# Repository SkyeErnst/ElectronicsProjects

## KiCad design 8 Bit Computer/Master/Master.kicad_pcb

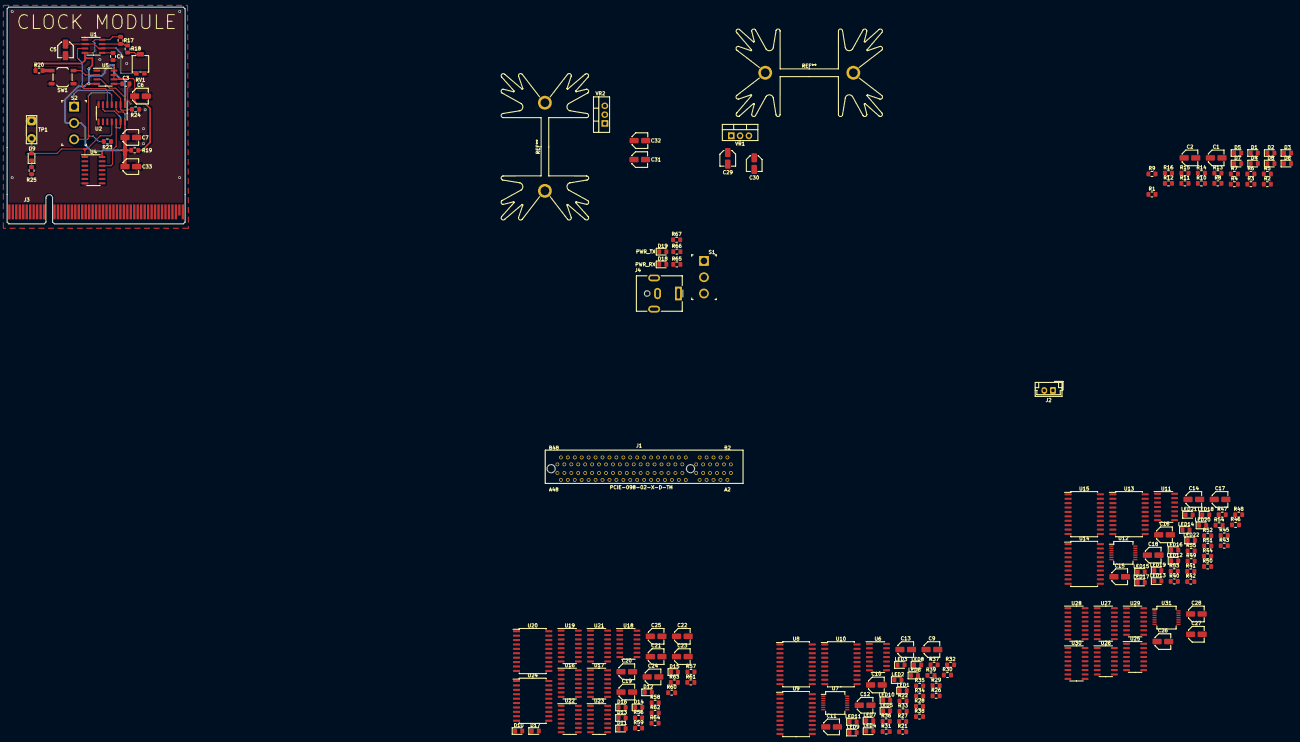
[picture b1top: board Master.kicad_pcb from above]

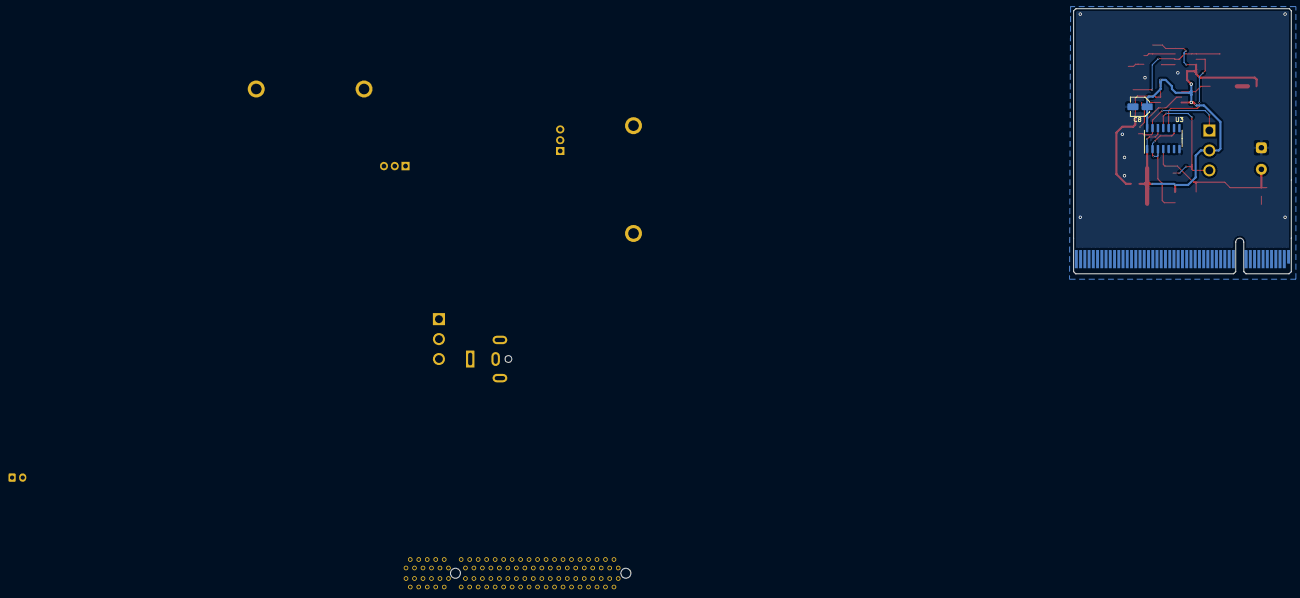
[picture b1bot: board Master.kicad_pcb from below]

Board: 2 copper layers, 51.3 x 62.5 mm, 183 parts (2 on the bottom side), 258 nets.

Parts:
C1, C2, C6: 0.1uF; C_Elec_4x5.4
C3, C4: 0.01uF; C_0805_2012Metric_Pad1.15x1.40mm_HandSolder
C5, C7, C8, C9, C10, C11, C12, C13, C14, C15, C16, C17, C18, C19, C20, C21, C22, C23, C24, C25, C26, C27, C28, C30, C32, C33: 1uF; C_Elec_4x5.4
C29, C31: 0.47uF; C_Elec_4x5.4
D1, D2, D3, D4, D5, D6, D7, D8, D18: GREEN; LED_0805_2012Metric_Pad1.15x1.40mm_HandSolder
D9, D10, D11, D12, D13, D14, D15, D16, D17: LED; LED_0805_2012Metric_Pad1.15x1.40mm_HandSolder
D19: RED; LED_0805_2012Metric_Pad1.15x1.40mm_HandSolder
J1: PCIE-098-02-X-D-TH
J2: PWR_IN 1x2 MALE; JST_EH_B2B-EH-A_1x02_P2.50mm_Vertical
J3: PCIE-098-02-X-D-TH; BUS_PCIexpress_x8
J4: PJ-063AH; BarrelJack_CUI_PJ-063AH_Horizontal
LED1, LED2, LED3, LED4, LED5, LED6, LED7, LED8, LED12, LED13, LED14, LED15, LED16, LED17, LED18, LED19: LED_Small; LED_0805_2012Metric_Pad1.15x1.40mm_HandSolder
LED9, LED20: BUS_READ; LED_0805_2012Metric_Pad1.15x1.40mm_HandSolder
LED10, LED21: REG_WRITE; LED_0805_2012Metric_Pad1.15x1.40mm_HandSolder
LED11, LED22: BUS_WRITE; LED_0805_2012Metric_Pad1.15x1.40mm_HandSolder
R1, R2, R3, R4, R5, R6, R7, R8, R21, R22, R25, R26, R27, R28, R29, R30, R31, R37, R38, R39, R40, R41, R42, R43, R44, R45, R46, R47, R53, R54, R55, R57, R58, R59, R60, R61, R62, R63, R64: 220; R_0805_2012Metric_Pad1.15x1.40mm_HandSolder
R9, R10, R11, R12, R13, R14, R15, R16: 10K; R_0805_2012Metric_Pad1.15x1.40mm_HandSolder
R17, R18, R20, R32, R33, R34, R35, R36, R48, R49, R50, R51, R52: 1k; R_0805_2012Metric_Pad1.15x1.40mm_HandSolder
R19: 1M; R_0805_2012Metric_Pad1.15x1.40mm_HandSolder
R23, R24: 2k; R_0805_2012Metric_Pad1.15x1.40mm_HandSolder
R56: 10k; R_0805_2012Metric_Pad1.15x1.40mm_HandSolder
R65, R66: 680; R_0805_2012Metric_Pad1.15x1.40mm_HandSolder
R67: 100K; R_0805_2012Metric_Pad1.15x1.40mm_HandSolder
RV1: 1M; Potentiometer_Bourns_3314G_Vertical
S1, S2: 100SP1T1B4M2QE; Toggle_Switch_100SP1T1B4M2QE
SW1: SW_Push; SW_SPST_TL3342
TP1: CLK_TP; TestPoint_2Pads_Pitch5.08mm_Drill1.3mm
U1, U5: NE555; SOIC-8_3.9x4.9mm_P1.27mm
U2: SN74LS08N; SOIC-14_3.9x8.7mm_P1.27mm
U3: SN74LS32N; SOIC-14_3.9x8.7mm_P1.27mm
U4: SN74LS04N; SOIC-14_3.9x8.7mm_P1.27mm
U6, U11, U25, U26, U29: 74LS08; SOIC-14_3.9x8.7mm_P1.27mm
U7, U12: 74LS04; SSOP-14_5.3x6.2mm_P0.65mm
U8, U10, U13, U15, U20, U24: 74LS245; SOIC-20W_7.5x12.8mm_P1.27mm
U9, U14: 74LS273; SOIC-20W_7.5x12.8mm_P1.27mm
U16: 74LS32; SOIC-14_3.9x8.7mm_P1.27mm
U17, U18, U22, U23: 74LS86; SOIC-14_3.9x8.7mm_P1.27mm
U19, U21, U27, U28, U30: 74LS283; SOIC-16_3.9x9.9mm_P1.27mm
U31: 74LS08; SSOP-14_5.3x6.2mm_P0.65mm
VR1, VR2: L78S05CV; TO-220-3_Vertical

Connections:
+5V: C1.1, C2.1, C7.1, C8.1, C9.1, C10.1, C11.1, C12.1, C13.1, C14.1, C15.1, C16.1, C17.1, C18.1, C30.1, C32.1, C33.1, J2.1, R17.1, R19.1, R20.1, R33.1, R49.1, R56.2, S2.2, U1.4, U1.8, U2.14, U3.14, U4.14, U5.4, U5.8, U6.14, U7.14, U8.1, U8.20, U9.20, U10.1, U10.20, U11.14, U12.14, U13.1, U13.20, U14.20, U15.1, U15.20, U20.1, U24.1, VR1.3, VR2.3
/BUS_0: R1.2, R9.1
/BUS_1: R2.2, R10.1
/BUS_2: R3.2, R11.1
/BUS_3: R4.2, R12.1
/BUS_4: R5.2, R13.1
/BUS_5: R6.2, R14.1
/BUS_6: R7.2, R15.1
/BUS_7: R8.2, R16.1
/Clock/CLK: D9.2, J3.A1, TP1.2, U2.11, U4.1
/Clock/HAULT: J3.A3, J3.B3, U4.13
/Clock/LNE_4: J3.A4, J3.B4
/Clock/LNE_5: J3.A5, J3.B5
/Clock/LNE_6: J3.A6, J3.B6
/Clock/LNE_7: J3.A7, J3.B7
/Clock/LNE_8: J3.A8, J3.B8
/Clock/LNE_9: J3.A9, J3.B9
/Clock/LNE_10: J3.A10, J3.B10
/Clock/LNE_11: J3.A11, J3.B11
/Clock/LNE_12: J3.A12, J3.B12
/Clock/LNE_13: J3.A13, J3.B13
/Clock/LNE_14: J3.A14, J3.B14
/Clock/LNE_15: J3.A15, J3.B15
/Clock/LNE_16: J3.A16, J3.B16
/Clock/LNE_17: J3.A17, J3.B17
/Clock/LNE_18: J3.A18, J3.B18
/Clock/LNE_19: J3.A19, J3.B19
/Clock/LNE_20: J3.A20, J3.B20
/Clock/LNE_21: J3.A21, J3.B21
/Clock/LNE_22: J3.A22, J3.B22
/Clock/LNE_23: J3.A23, J3.B23
/Clock/LNE_24: J3.A24, J3.B24
/Clock/LNE_25: J3.A25, J3.B25
/Clock/LNE_26: J3.A26, J3.B26
/Clock/LNE_27: J3.A27, J3.B27
/Clock/LNE_28: J3.A28, J3.B28
/Clock/LNE_29: J3.A29, J3.B29
/Clock/LNE_30: J3.A30, J3.B30
/Clock/LNE_31: J3.A31, J3.B31
/Clock/LNE_32: J3.A32, J3.B32
/Clock/LNE_33: J3.A33, J3.B33
/Clock/LNE_34: J3.A34, J3.B34
/Clock/LNE_35: J3.A35, J3.B35
/Clock/LNE_36: J3.A36, J3.B36
/Clock/LNE_37: J3.A37, J3.B37
/Clock/LNE_38: J3.A38, J3.B38
/Clock/LNE_39: J3.A39, J3.B39
/Clock/LNE_40: J3.A40, J3.B40
/Clock/LNE_41: J3.A41, J3.B41
/Clock/LNE_42: J3.A42, J3.B42
/Clock/LNE_43: J3.A43, J3.B43
/Clock/LNE_44: J3.A44, J3.B44
/Clock/LNE_45: J3.A45, J3.B45
/Clock/LNE_46: J3.A46, J3.B46
/Clock/LNE_47: J3.A47, J3.B47
/Clock/LNE_48: J3.A48, J3.B48
/Clock/LNE_49: J3.A49, J3.B49
/Clock/~CLK: J3.A2, J3.B2, U4.2
/Math Unit A/REG_AA/ALU_AA_0: R21.2, U9.2, U10.2, U17.2, U25.2, U26.2, U29.2, U31.2
/Math Unit A/REG_AA/ALU_AA_1: R22.2, U6.5, U9.5, U10.3, U11.5, U17.5, U25.5, U26.5
/Math Unit A/REG_AA/ALU_AA_2: R26.2, U6.10, U9.6, U10.4, U11.10, U17.10, U25.10, U26.10
/Math Unit A/REG_AA/ALU_AA_3: R27.2, U6.13, U9.9, U10.5, U11.13, U17.13, U25.13, U26.13
/Math Unit A/REG_AA/ALU_AA_4: R28.2, U9.12, U10.6, U22.2
/Math Unit A/REG_AA/ALU_AA_5: R29.2, U9.15, U10.7, U22.5
/Math Unit A/REG_AA/ALU_AA_6: R30.2, U9.16, U10.8, U22.10
/Math Unit A/REG_AA/ALU_AA_7: R31.2, U9.19, U10.9, U22.13
/Math Unit A/REG_AA/BUS_0: U8.2, U10.18
/Math Unit A/REG_AA/BUS_1: U8.3, U10.17
/Math Unit A/REG_AA/BUS_2: U8.4, U10.16
/Math Unit A/REG_AA/BUS_3: U8.5, U10.15
/Math Unit A/REG_AA/BUS_4: U8.6, U10.14
/Math Unit A/REG_AA/BUS_5: U8.7, U10.13
/Math Unit A/REG_AA/BUS_6: U8.8, U10.12
/Math Unit A/REG_AA/BUS_7: U8.9, U10.11
/Math Unit A/REG_AA/CLK: R36.2, U6.2
/Math Unit A/REG_AA/REG_A_BUS_READ: R32.2, R35.2, U6.1, U7.1, U8.19
/Math Unit A/REG_AA/REG_A_BUS_WRITE: U7.3, U10.19
/Math Unit A/REG_AA/RESET: R33.2, U9.1
/Math Unit A/REG_AB/ALU_AB_0: R40.2, U14.2, U15.2, U18.2, U25.4, U25.9, U25.12, U29.1
/Math Unit A/REG_AB/ALU_AB_1: R41.2, U14.5, U15.3, U18.5, U26.4, U26.9, U26.12, U31.1
/Math Unit A/REG_AB/ALU_AB_2: R42.2, U11.4, U11.9, U11.12, U14.6, U15.4, U18.10, U26.1
/Math Unit A/REG_AB/ALU_AB_3: R43.2, U6.4, U6.9, U6.12, U14.9, U15.5, U18.13, U25.1
/Math Unit A/REG_AB/ALU_AB_4: R44.2, U14.12, U15.6, U23.2
/Math Unit A/REG_AB/ALU_AB_5: R45.2, U14.15, U15.7, U23.5
/Math Unit A/REG_AB/ALU_AB_6: R46.2, U14.16, U15.8, U23.10
/Math Unit A/REG_AB/ALU_AB_7: R47.2, U14.19, U15.9, U23.13
/Math Unit A/REG_AB/BUS_0: U13.2, U15.18
/Math Unit A/REG_AB/BUS_1: U13.3, U15.17
/Math Unit A/REG_AB/BUS_2: U13.4, U15.16
/Math Unit A/REG_AB/BUS_3: U13.5, U15.15
/Math Unit A/REG_AB/BUS_4: U13.6, U15.14
/Math Unit A/REG_AB/BUS_5: U13.7, U15.13
/Math Unit A/REG_AB/BUS_6: U13.8, U15.12
/Math Unit A/REG_AB/BUS_7: U13.9, U15.11
/Math Unit A/REG_AB/CLK: R52.2, U11.2
/Math Unit A/REG_AB/REG_B_BUS_READ: R48.2, R51.2, U11.1, U12.1, U13.19
/Math Unit A/REG_AB/REG_B_BUS_WRITE: R50.2, U12.3, U15.19
/Math Unit A/REG_AB/RESET: R49.2, U14.1
/Math Unit A/sheet5E11EF59/BUS_0: U20.18, U24.18
/Math Unit A/sheet5E11EF59/BUS_1: U20.17, U24.17
/Math Unit A/sheet5E11EF59/BUS_2: U20.16, U24.16
/Math Unit A/sheet5E11EF59/BUS_3: U20.15, U24.15
/Math Unit A/sheet5E11EF59/BUS_4: U20.14, U24.14
/Math Unit A/sheet5E11EF59/BUS_5: U20.13, U24.13
/Math Unit A/sheet5E11EF59/BUS_6: U20.12, U24.12
/Math Unit A/sheet5E11EF59/BUS_7: U20.11, U24.11
/Math Unit A/sheet5E11EF59/Multiplier/MUL_0: U24.2, U29.3
/Math Unit A/sheet5E11EF59/Multiplier/MUL_1: U24.3, U30.4
/Math Unit A/sheet5E11EF59/Multiplier/MUL_2: U24.4, U28.4
/Math Unit A/sheet5E11EF59/Multiplier/MUL_3: U24.5, U27.4
/Math Unit A/sheet5E11EF59/Multiplier/MUL_4: U24.6, U27.1
/Math Unit A/sheet5E11EF59/Multiplier/MUL_5: U24.7, U27.13
/Math Unit A/sheet5E11EF59/Multiplier/MUL_6: U24.8, U27.10
/Math Unit A/sheet5E11EF59/Multiplier/MUL_7: U24.9, U27.9
/Math Unit A/sheet5E11EF59/SUBa: U16.1, U17.1, U17.4, U17.9, U17.12, U22.1, U22.4, U22.9, U22.12
/Math Unit A/sheet5E11EF59/SUBb: U16.2, U18.1, U18.4, U18.9, U18.12, U23.1, U23.4, U23.9, U23.12
/Math Unit A/sheet5E11EF59/~EOas: R56.1, U20.19
/POWR/PWR_AFT_SW: C29.1, C31.1, R66.2, S1.2, VR1.1, VR2.1
/POWR/PWR_IN: J4.1, R65.2, S1.3
GND: C1.2, C2.2, C3.2, C4.2, C5.2, C6.2, C7.2, C8.2, C9.2, C10.2, C11.2, C12.2, C13.2, C14.2, C15.2, C16.2, C17.2, C18.2, C19.2, C20.2, C21.2, C22.2, C23.2, C24.2, C25.2, C26.2, C27.2, C28.2, C29.2, C30.2, C31.2, C32.2, C33.2, D1.1, D2.1, D3.1, D4.1, D5.1, D6.1, D7.1, D8.1, D10.1, D11.1, D12.1, D13.1, D14.1, D15.1, D16.1, D17.1, D18.1, D19.1, J2.2, J4.2, LED1.1, LED2.1, LED3.1, LED4.1, LED5.1, LED6.1, LED7.1, LED8.1, LED9.1, LED10.1, LED11.1, LED12.1, LED13.1, LED14.1, LED15.1, LED16.1, LED17.1, LED18.1, LED19.1, LED20.1, LED21.1, LED22.1, R9.2, R10.2, R11.2, R12.2, R13.2, R14.2, R15.2, R16.2, R23.1, R24.1, R25.1, R32.1, R34.1, R35.1, R36.1, R48.1, R50.1, R51.1, R52.1, R67.1, SW1.1, TP1.1, U1.1, U2.7, U3.7, U4.7, U5.1, U6.7, U7.7, U8.10, U9.10, U10.10, U11.7, U12.7, U13.10, U14.10, U15.10, U16.7, U17.7, U18.7, U19.8, U20.10, U21.8, U24.10, U27.7, U27.8, U28.7, U28.8, U30.7, U30.8, U30.12, VR1.2, VR2.2
unnamed: C3.1, U5.5
unnamed: C4.1, U1.5
unnamed: C5.1, RV1.1, U1.2, U1.6
unnamed: C6.1, R19.2, U5.6, U5.7
unnamed: C19.1, U16.14
unnamed: C20.1, U17.14
unnamed: C21.1, U18.14
unnamed: C22.1, U19.16
unnamed: C23.1, U20.20
unnamed: C24.1, U21.16
unnamed: C25.1, U24.20
unnamed: C26.1, U27.16
unnamed: C27.1, U28.16
unnamed: C28.1, U30.16
unnamed: D1.2, R1.1
unnamed: D2.2, R2.1
unnamed: D3.2, R3.1
unnamed: D4.2, R4.1
unnamed: D5.2, R5.1
unnamed: D6.2, R6.1
unnamed: D7.2, R7.1
unnamed: D8.2, R8.1
unnamed: D9.1, R25.2
unnamed: D10.2, R57.2
unnamed: D11.2, R58.2
unnamed: D12.2, R59.2
unnamed: D13.2, R60.2
unnamed: D14.2, R61.2
unnamed: D15.2, R62.2
unnamed: D16.2, R63.2
unnamed: D17.2, R64.2
unnamed: D18.2, R65.1
unnamed: D19.2, R66.1
unnamed: LED1.2, R21.1
unnamed: LED2.2, R22.1
unnamed: LED3.2, R26.1
unnamed: LED4.2, R27.1
unnamed: LED5.2, R28.1
unnamed: LED6.2, R29.1
unnamed: LED7.2, R30.1
unnamed: LED8.2, R31.1
unnamed: LED9.2, R37.1
unnamed: LED10.2, R38.1
unnamed: LED11.2, R39.1
unnamed: LED12.2, R40.1
unnamed: LED13.2, R41.1
unnamed: LED14.2, R42.1
unnamed: LED15.2, R43.1
unnamed: LED16.2, R44.1
unnamed: LED17.2, R45.1
unnamed: LED18.2, R46.1
unnamed: LED19.2, R47.1
unnamed: LED20.2, R53.1
unnamed: LED21.2, R54.1
unnamed: LED22.2, R55.1
unnamed: R17.2, R18.2, U1.7
unnamed: R18.1, RV1.2
unnamed: R20.2, SW1.2, U5.2
unnamed: R23.2, S2.3, U2.4
unnamed: R24.2, S2.1, U2.2
unnamed: R37.2, U7.2
unnamed: R38.2, U6.3, U9.11
unnamed: R39.2, U7.4
unnamed: R53.2, U12.2
unnamed: R54.2, U11.3, U14.11
unnamed: R55.2, U12.4
unnamed: R57.1, U19.4, U20.2
unnamed: R58.1, U19.1, U20.3
unnamed: R59.1, U19.13, U20.4
unnamed: R60.1, U19.10, U20.5
unnamed: R61.1, U20.6, U21.4
unnamed: R62.1, U20.7, U21.1
unnamed: R63.1, U20.8, U21.13
unnamed: R64.1, U20.9, U21.10
unnamed: R67.2, S1.1
unnamed: U1.3, U2.5
unnamed: U2.1, U5.3
unnamed: U2.3, U3.1
unnamed: U2.6, U3.2
unnamed: U2.12, U4.12
unnamed: U2.13, U3.3
unnamed: U8.11, U9.18
unnamed: U8.12, U9.17
unnamed: U8.13, U9.14
unnamed: U8.14, U9.13
unnamed: U8.15, U9.8
unnamed: U8.16, U9.7
unnamed: U8.17, U9.4
unnamed: U8.18, U9.3
unnamed: U11.6, U28.3
unnamed: U11.8, U28.14
unnamed: U11.11, U28.12
unnamed: U13.11, U14.18
unnamed: U13.12, U14.17
unnamed: U13.13, U14.14
unnamed: U13.14, U14.13
unnamed: U13.15, U14.8
unnamed: U13.16, U14.7
unnamed: U13.17, U14.4
unnamed: U13.18, U14.3
unnamed: U16.3, U19.7
unnamed: U17.3, U19.5
unnamed: U17.6, U19.3
unnamed: U17.8, U19.14
unnamed: U17.11, U19.12
unnamed: U18.3, U19.6
unnamed: U18.6, U19.2
unnamed: U18.8, U19.15
unnamed: U18.11, U19.11
unnamed: U19.9, U21.7
unnamed: U21.2, U23.6
unnamed: U21.3, U22.6
unnamed: U21.5, U22.3
unnamed: U21.6, U23.3
unnamed: U21.11, U23.11
unnamed: U21.12, U22.11
unnamed: U21.14, U22.8
unnamed: U21.15, U23.8
unnamed: U25.3, U27.5
unnamed: U25.6, U30.5
unnamed: U25.8, U30.3
unnamed: U25.11, U30.14
unnamed: U26.3, U28.5
unnamed: U26.6, U30.2
unnamed: U26.8, U30.15
unnamed: U26.11, U30.11
unnamed: U27.2, U28.13
unnamed: U6.6, U27.3
unnamed: U27.6, U28.1
unnamed: U27.11, U28.9
unnamed: U6.11, U27.12
unnamed: U6.8, U27.14
unnamed: U27.15, U28.10
unnamed: U28.2, U30.13
unnamed: U28.6, U30.1
unnamed: U28.11, U30.9
unnamed: U28.15, U30.10
unnamed: U30.6, U31.3

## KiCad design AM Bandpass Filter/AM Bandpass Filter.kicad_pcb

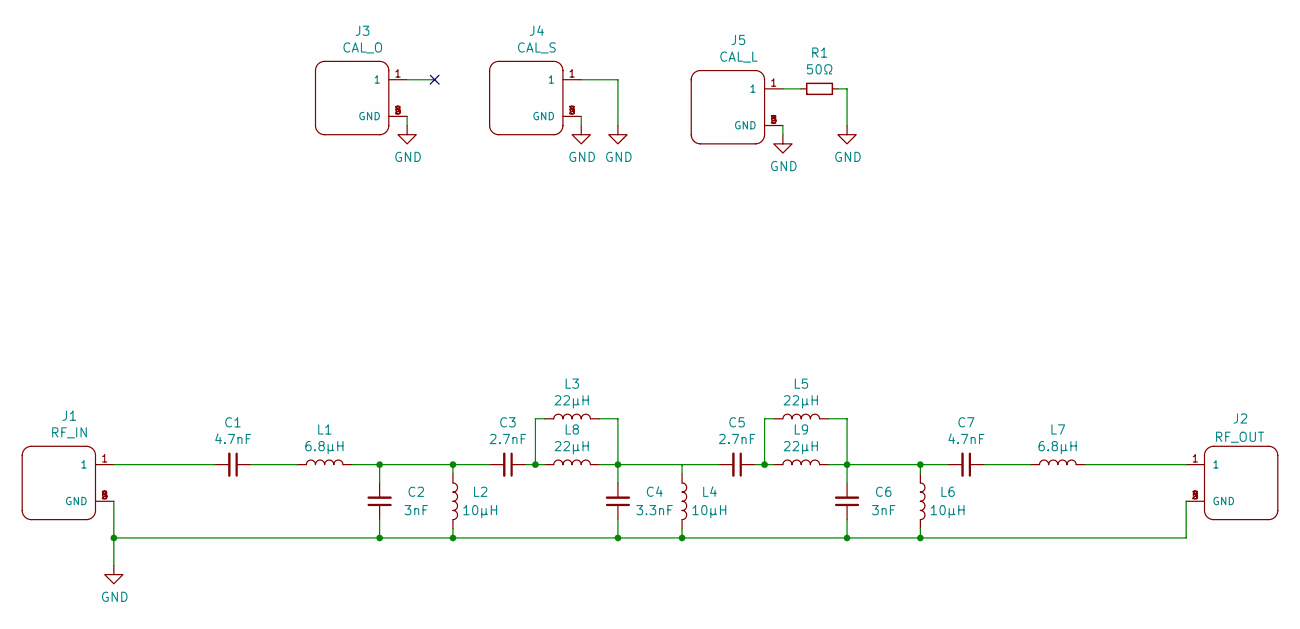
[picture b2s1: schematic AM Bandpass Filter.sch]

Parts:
C1, C7: 4.7nF; C_0805_2012Metric_Pad1.15x1.40mm_HandSolder
C2, C6: 3nF; C_0805_2012Metric_Pad1.15x1.40mm_HandSolder
C3, C5: 2.7nF; C_0805_2012Metric_Pad1.15x1.40mm_HandSolder
C4: 3.3nF; C_0805_2012Metric_Pad1.15x1.40mm_HandSolder
J1: RF_IN; TE_5-1634503-1
J2: RF_OUT; TE_5-1634503-1
J3: CAL_O; TE_5-1634503-1
J4: CAL_S; TE_5-1634503-1
J5: CAL_L; TE_5-1634503-1
L1, L7: 6.8µH; L_0805_2012Metric_Pad1.15x1.40mm_HandSolder
L2, L4, L6: 10µH; L_0805_2012Metric_Pad1.15x1.40mm_HandSolder
L3, L5, L8, L9: 22µH; L_0805_2012Metric_Pad1.15x1.40mm_HandSolder
R1: 50Ω; R_1206_3216Metric_Pad1.42x1.75mm_HandSolder

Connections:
GND: C2.1, C4.1, C6.1, J1.2 (GND), J1.3 (GND), J1.4 (GND), J1.5 (GND), J2.2 (GND), J2.3 (GND), J2.4 (GND), J2.5 (GND), J3.2 (GND), J3.3 (GND), J3.4 (GND), J3.5 (GND), J4.1, J4.2 (GND), J4.3 (GND), J4.4 (GND), J4.5 (GND), J5.2 (GND), J5.3 (GND), J5.4 (GND), J5.5 (GND), L2.2, L4.2, L6.2, R1.2
unnamed: C1.1, L1.1
unnamed: C1.2, J1.1
unnamed: C2.2, C3.2, L1.2, L2.1
unnamed: C3.1, L3.1, L8.1
unnamed: C4.2, C5.2, L3.2, L4.1, L8.2
unnamed: C5.1, L5.1, L9.1
unnamed: C6.2, C7.2, L5.2, L6.1, L9.2
unnamed: C7.1, L7.1
unnamed: J2.1, L7.2
unnamed: J5.1, R1.1

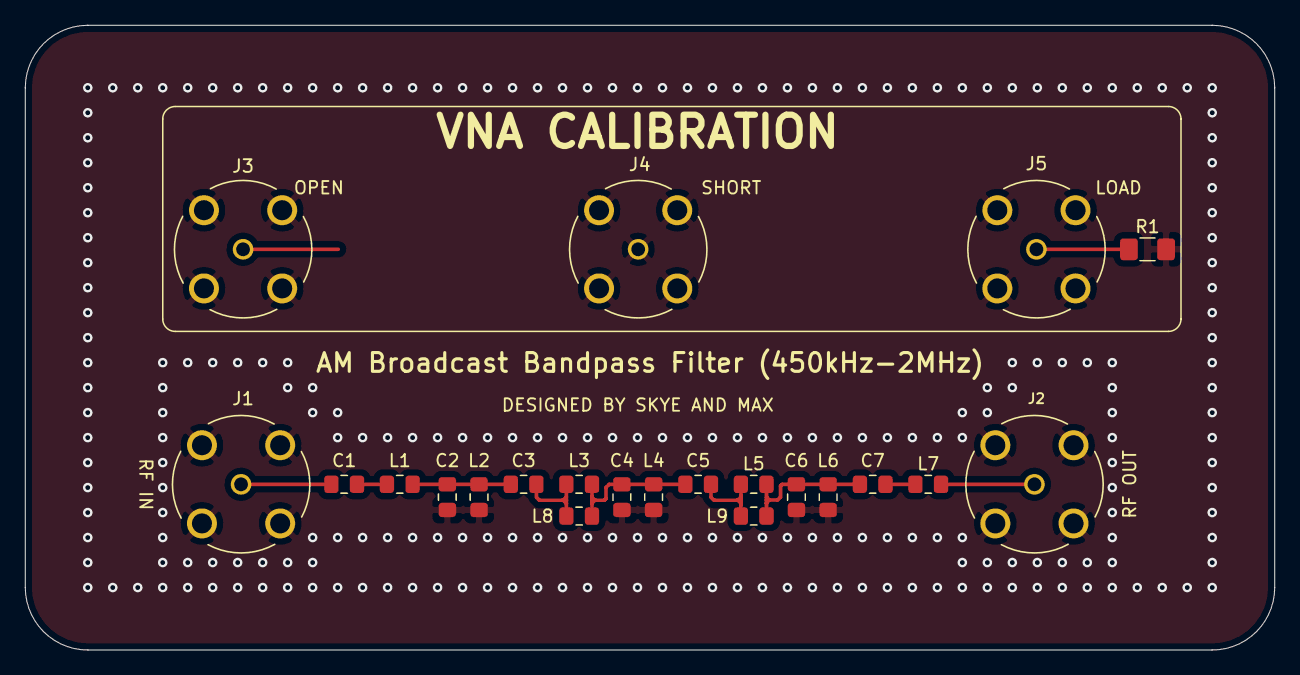
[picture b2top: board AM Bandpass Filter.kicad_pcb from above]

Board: 4 copper layers, 100.0 x 50.0 mm, 22 parts (0 on the bottom side), 11 nets.

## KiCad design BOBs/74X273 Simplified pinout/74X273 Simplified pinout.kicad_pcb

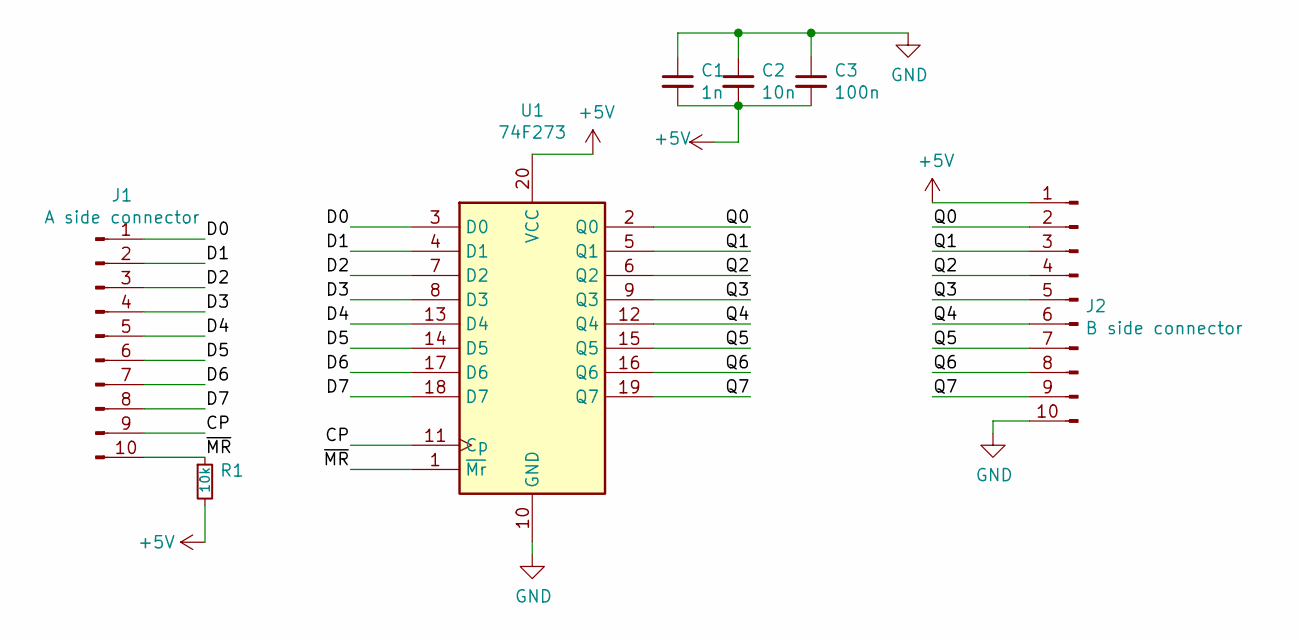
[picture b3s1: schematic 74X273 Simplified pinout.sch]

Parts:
C1: 1n; C_0805_2012Metric_Pad1.15x1.40mm_HandSolder
C2: 10n; C_0805_2012Metric_Pad1.15x1.40mm_HandSolder
C3: 100n; C_0805_2012Metric_Pad1.15x1.40mm_HandSolder
J1: A side connector; PinHeader_1x10_P2.54mm_Vertical
J2: B side connector; PinHeader_1x10_P2.54mm_Vertical
R1: 10k; R_0805_2012Metric
U1: 74F273; SOIC-20W_7.5x12.8mm_P1.27mm

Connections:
+5V: C1.2, C2.2, C3.2, J2.1, R1.2, U1.20 (VCC)
/CP: J1.9, U1.11 (Cp)
/D0: J1.1, U1.3 (D0)
/D1: J1.2, U1.4 (D1)
/D2: J1.3, U1.7 (D2)
/D3: J1.4, U1.8 (D3)
/D4: J1.5, U1.13 (D4)
/D5: J1.6, U1.14 (D5)
/D6: J1.7, U1.17 (D6)
/D7: J1.8, U1.18 (D7)
/Q0: J2.2, U1.2 (Q0)
/Q1: J2.3, U1.5 (Q1)
/Q2: J2.4, U1.6 (Q2)
/Q3: J2.5, U1.9 (Q3)
/Q4: J2.6, U1.12 (Q4)
/Q5: J2.7, U1.15 (Q5)
/Q6: J2.8, U1.16 (Q6)
/Q7: J2.9, U1.19 (Q7)
/~MR: J1.10, R1.1, U1.1 (~Mr)
GND: C1.1, C2.1, C3.1, J2.10, U1.10 (GND)

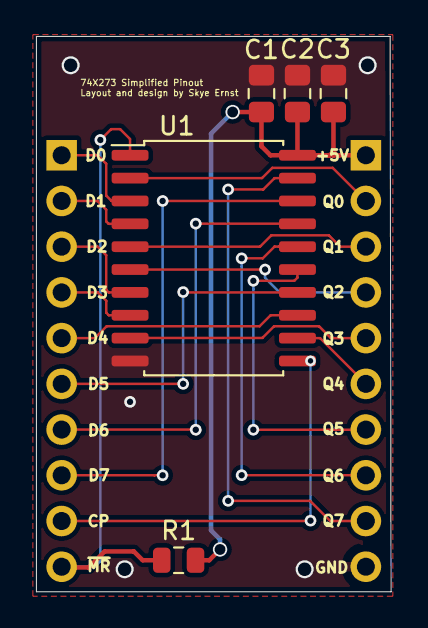
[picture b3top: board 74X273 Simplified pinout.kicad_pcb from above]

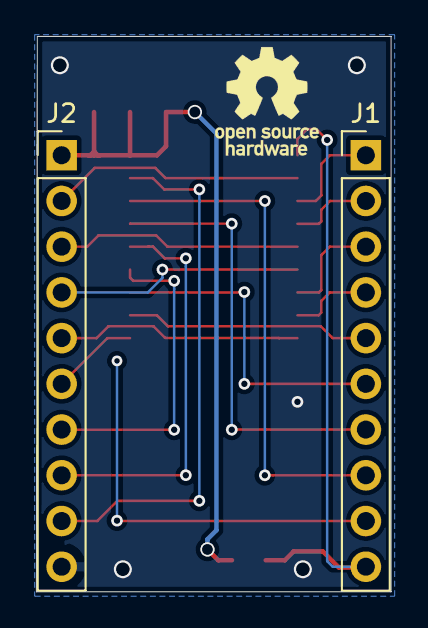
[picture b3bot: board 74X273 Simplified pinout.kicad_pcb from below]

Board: 2 copper layers, 19.7 x 30.8 mm, 7 parts (2 on the bottom side), 20 nets.

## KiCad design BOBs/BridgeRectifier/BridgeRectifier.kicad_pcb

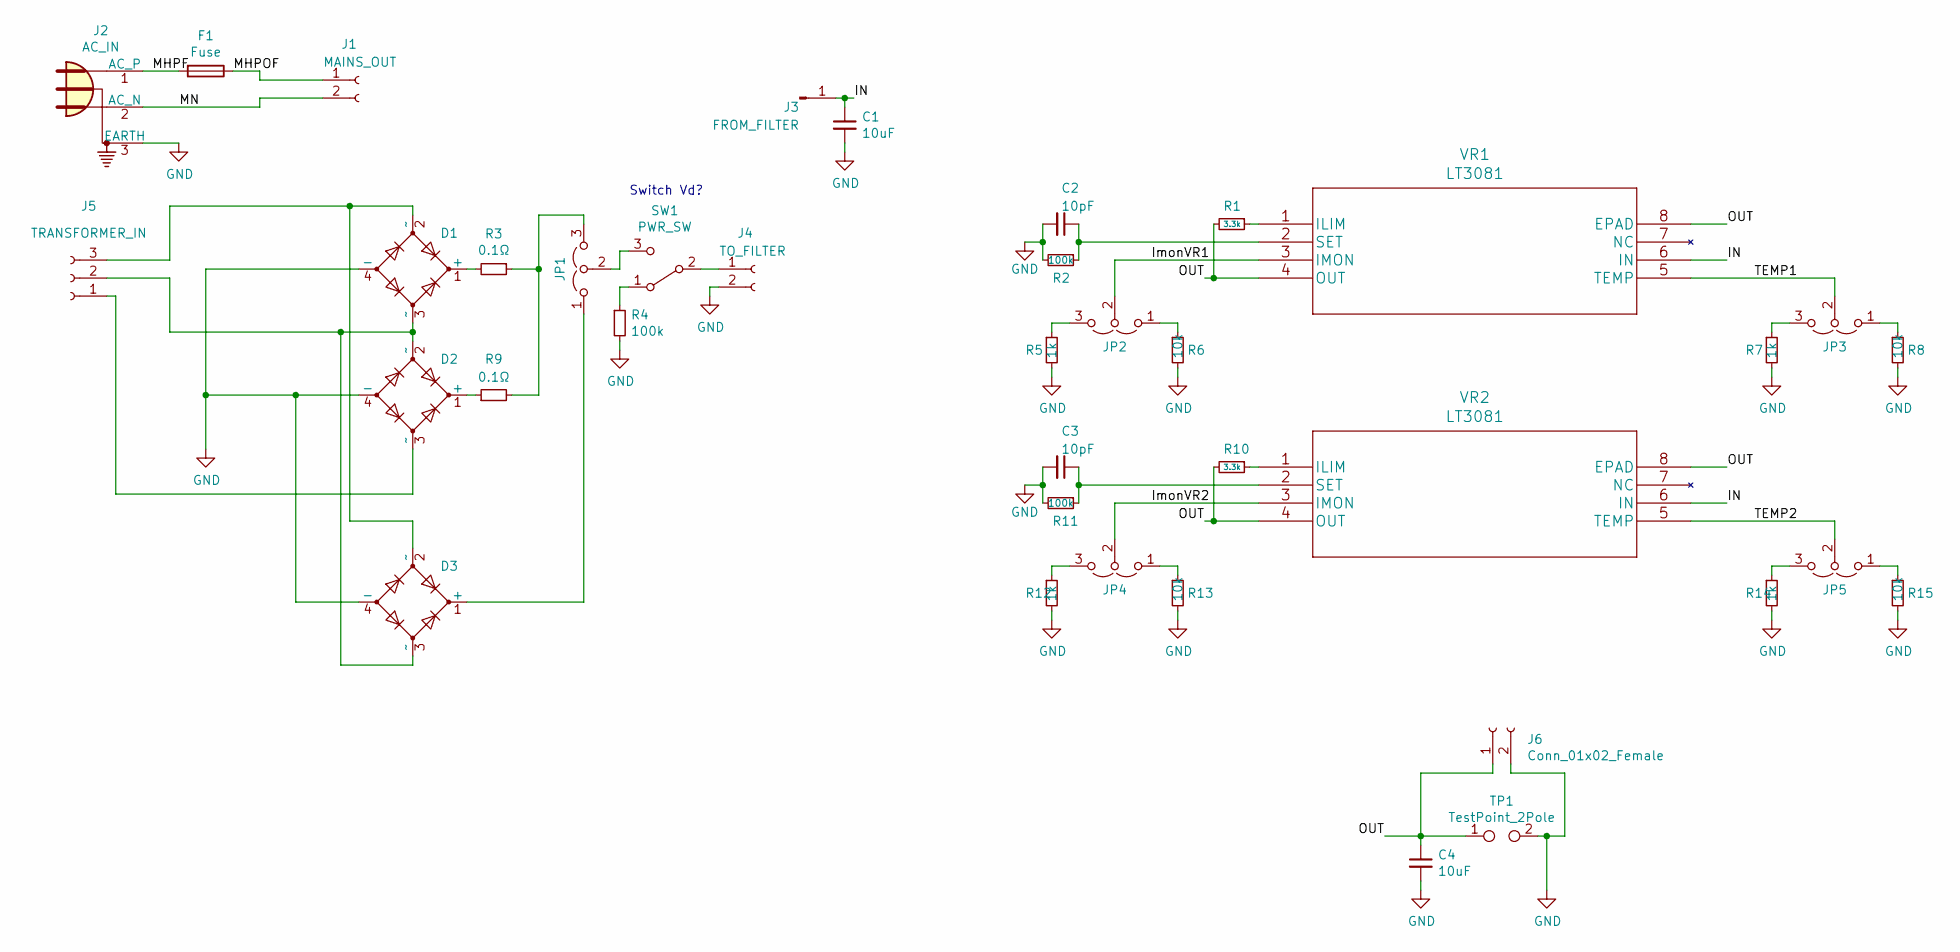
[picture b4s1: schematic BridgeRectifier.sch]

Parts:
C1, C4: 10uF; C_1210_3225Metric
C2, C3: 10pF; C_Disc_D3.0mm_W2.0mm_P2.50mm
D1, D2, D3: D_Bridge_+AA-; Diode_Bridge_Vishay_GBU
F1: Fuse; Fuseholder_Cylinder-5x20mm_Schurter_0031_8201_Horizontal_Op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
J1: MAINS_OUT; SolderWirePad_1x02_P3.81mm_Drill1.2mm
J2: AC_IN; SolderWirePad_1x03_P4.445mm_Drill1.5mm
J3: FROM_FILTER; PinHeader_1x01_P2.54mm_Vertical
J4: TO_FILTER; PinHeader_1x02_P2.54mm_Vertical
J5: TRANSFORMER_IN; SolderWirePad_1x03_P3.175mm_Drill0.8mm
J6: Conn_01x02_Female; PinHeader_1x02_P2.54mm_Vertical
JP1, JP2, JP3, JP4, JP5: Jumper_3_Open; SolderJumper-3_P1.3mm_Open_RoundedPad1.0x1.5mm
R1, R10: 3.3k; R_Axial_DIN0309_L9.0mm_D3.2mm_P15.24mm_Horizontal
R2, R11: 100k; R_Axial_DIN0309_L9.0mm_D3.2mm_P15.24mm_Horizontal; digikey P20200CT-ND
R3, R9: 0.1Ω; TO-220-2_Vertical
R4: 100k; R_Axial_DIN0309_L9.0mm_D3.2mm_P15.24mm_Horizontal
R5, R7, R12, R14: 1k; R_0805_2012Metric
R6, R8, R13, R15: 10k; R_0805_2012Metric
SW1: PWR_SW; Switch_Toggle_ATE1D-2M3-10-Z
TP1: TestPoint_2Pole; TestPoint_2Pads_Pitch5.08mm_Drill1.3mm
VR1, VR2: LT3081; TO-220-7_P2.54x3.7mm_StaggerEven_Lead3.8mm_Vertical

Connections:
/IN: C1.1, J3.1, VR1.6 (IN), VR2.6 (IN)
/ImonVR1: JP2.2 (C), VR1.3 (IMON)
/ImonVR2: JP4.2 (C), VR2.3 (IMON)
/MHPF: F1.2, J2.1 (AC_P)
/MHPOF: F1.1, J1.1
/MN: J1.2, J2.2 (AC_N)
/OUT: C4.1, J6.1, R1.2, R10.2, TP1.1, VR1.4 (OUT), VR1.8 (EPAD), VR2.4 (OUT), VR2.8 (EPAD)
/TEMP1: JP3.2 (C), VR1.5 (TEMP)
/TEMP2: JP5.2 (C), VR2.5 (TEMP)
GND: C1.2, C2.2, C3.2, C4.2, D1.4 (-), D2.4 (-), D3.4 (-), J2.3 (EARTH), J4.2, J6.2, R2.2, R4.2, R5.2, R6.2, R7.2, R8.2, R11.2, R12.2, R13.2, R14.2, R15.2, TP1.2
unnamed: C2.1, R2.1, VR1.2 (SET)
unnamed: C3.1, R11.1, VR2.2 (SET)
unnamed: D1.1 (+), R3.2
unnamed: D1.2 (~~), D3.2 (~~), J5.3
unnamed: D1.3 (~~), D2.2 (~~), D3.3 (~~), J5.2
unnamed: D2.1 (+), R9.1
unnamed: D2.3 (~~), J5.1
unnamed: D3.1 (+), JP1.1 (A)
unnamed: J4.1, SW1.2 (B)
unnamed: JP1.2 (C), SW1.3 (C)
unnamed: JP1.3 (B), R3.1, R9.2
unnamed: JP2.1 (A), R6.1
unnamed: JP2.3 (B), R5.1
unnamed: JP3.1 (A), R8.1
unnamed: JP3.3 (B), R7.1
unnamed: JP4.1 (A), R13.1
unnamed: JP4.3 (B), R12.1
unnamed: JP5.1 (A), R15.1
unnamed: JP5.3 (B), R14.1
unnamed: R1.1, VR1.1 (ILIM)
unnamed: R4.1, SW1.1 (A)
unnamed: R10.1, VR2.1 (ILIM)

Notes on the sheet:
Switch Vd?

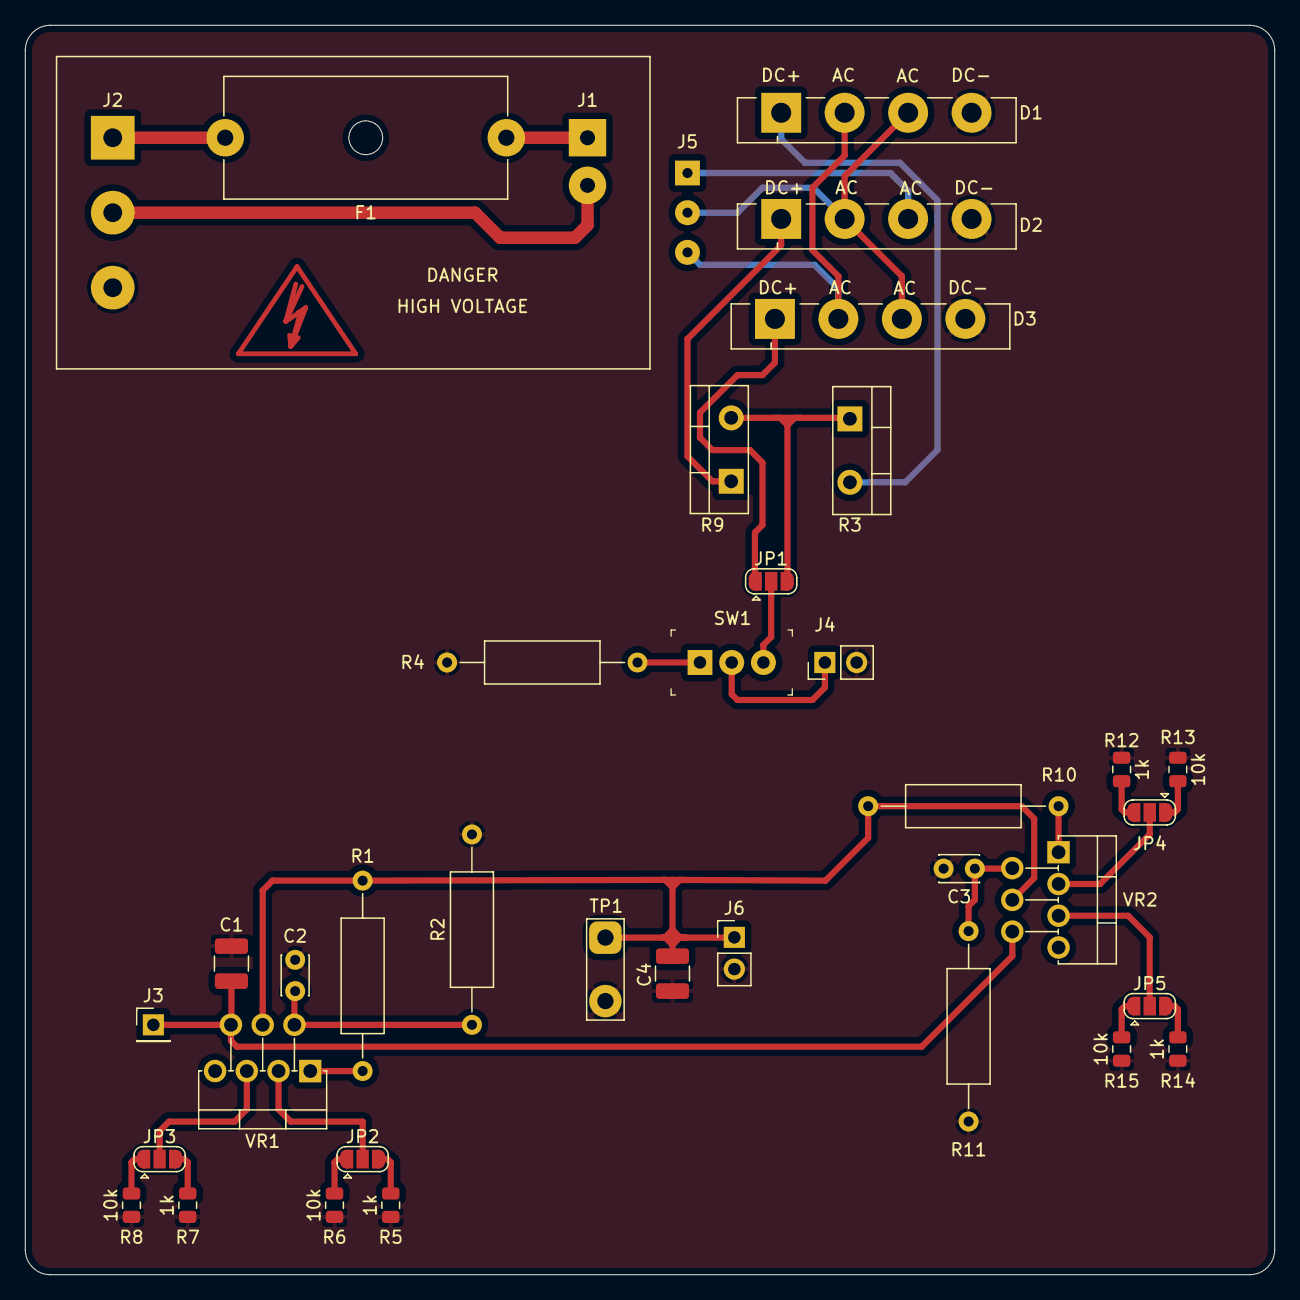
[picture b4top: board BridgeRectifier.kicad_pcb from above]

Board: 2 copper layers, 100.0 x 100.0 mm, 38 parts (0 on the bottom side), 32 nets.

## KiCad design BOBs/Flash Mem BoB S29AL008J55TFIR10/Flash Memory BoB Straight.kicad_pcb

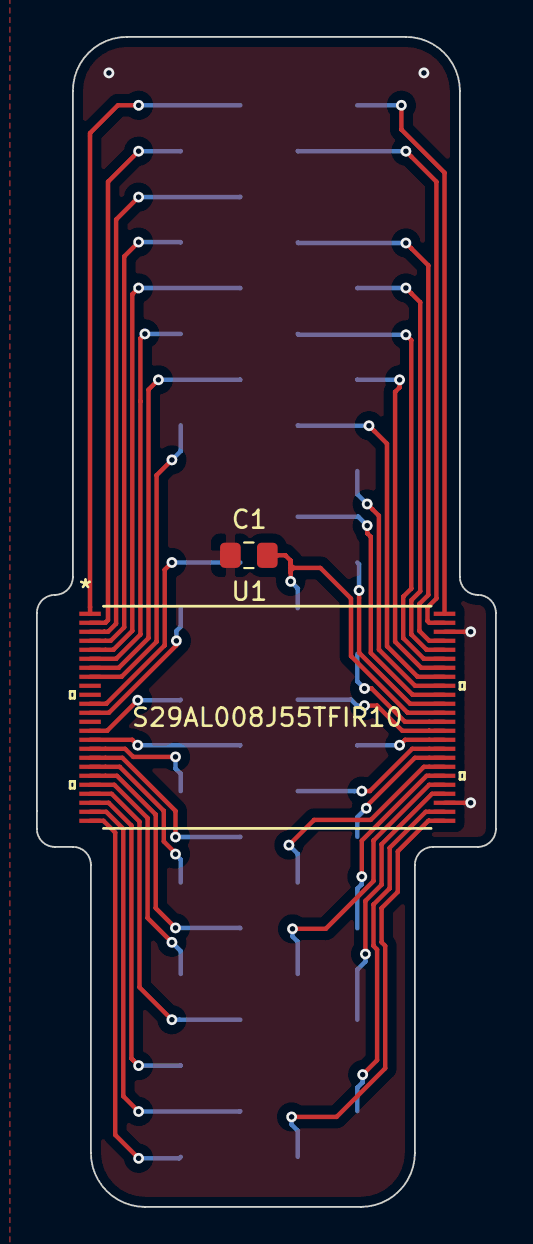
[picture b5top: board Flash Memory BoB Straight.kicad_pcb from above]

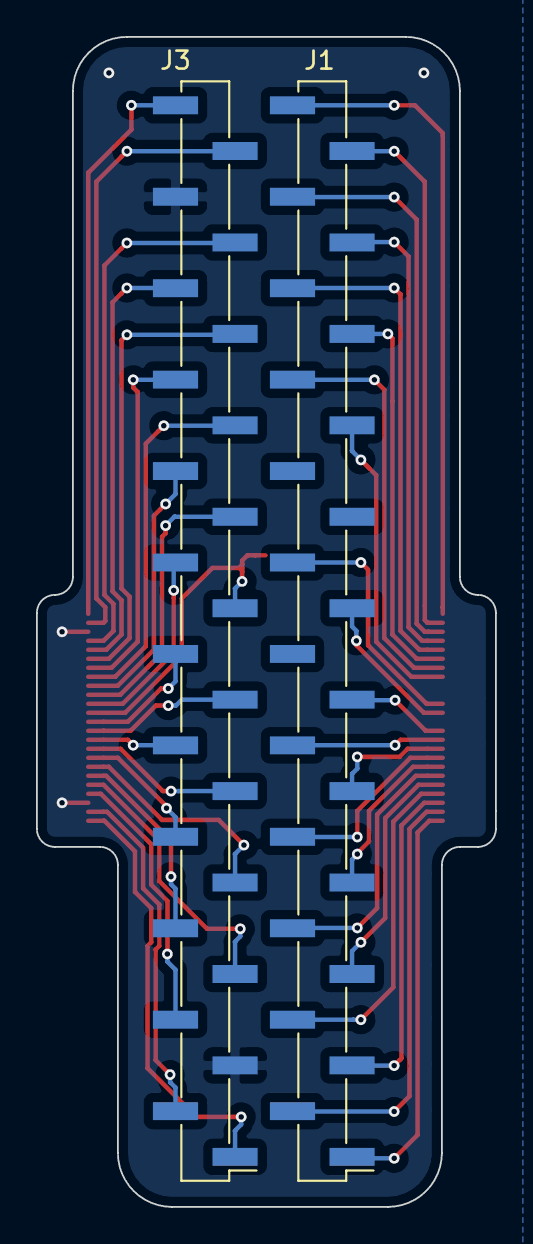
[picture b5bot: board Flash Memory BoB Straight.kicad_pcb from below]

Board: 2 copper layers, 25.5 x 65.0 mm, 4 parts (2 on the bottom side), 44 nets.

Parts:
C1: 1uF; C_0805_2012Metric_Pad1.15x1.40mm_HandSolder
J1, J3: Conn_01x24; PinHeader_1x24_P2.54mm_Vertical_SMD_Pin1Left
U1: S29AL008J55TFIR10

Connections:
+3V3: C1.2, J3.13, U1.37
GND: C1.1, J3.3, J3.22, U1.27, U1.46
unnamed: J1.1, U1.24
unnamed: J1.2, U1.23
unnamed: J1.3, U1.22
unnamed: J1.4, U1.21
unnamed: J1.5, U1.20
unnamed: J1.6, U1.19
unnamed: J1.7, U1.18
unnamed: J1.8, U1.17
unnamed: J1.9, U1.16
unnamed: J1.10, U1.15
unnamed: J1.11, U1.14
unnamed: J1.13, U1.12
unnamed: J1.14, U1.11
unnamed: J1.17, U1.8
unnamed: J1.18, U1.7
unnamed: J1.19, U1.6
unnamed: J1.20, U1.5
unnamed: J1.21, U1.4
unnamed: J1.22, U1.3
unnamed: J1.23, U1.2
unnamed: J1.24, U1.1
unnamed: J3.1, U1.25
unnamed: J3.2, U1.26
unnamed: J3.4, U1.28
unnamed: J3.5, U1.29
unnamed: J3.6, U1.30
unnamed: J3.7, U1.31
unnamed: J3.8, U1.32
unnamed: J3.9, U1.33
unnamed: J3.10, U1.34
unnamed: J3.11, U1.35
unnamed: J3.12, U1.36
unnamed: J3.14, U1.38
unnamed: J3.15, U1.39
unnamed: J3.16, U1.40
unnamed: J3.17, U1.41
unnamed: J3.18, U1.42
unnamed: J3.19, U1.43
unnamed: J3.20, U1.44
unnamed: J3.21, U1.45
unnamed: J3.23, U1.47
unnamed: J3.24, U1.48

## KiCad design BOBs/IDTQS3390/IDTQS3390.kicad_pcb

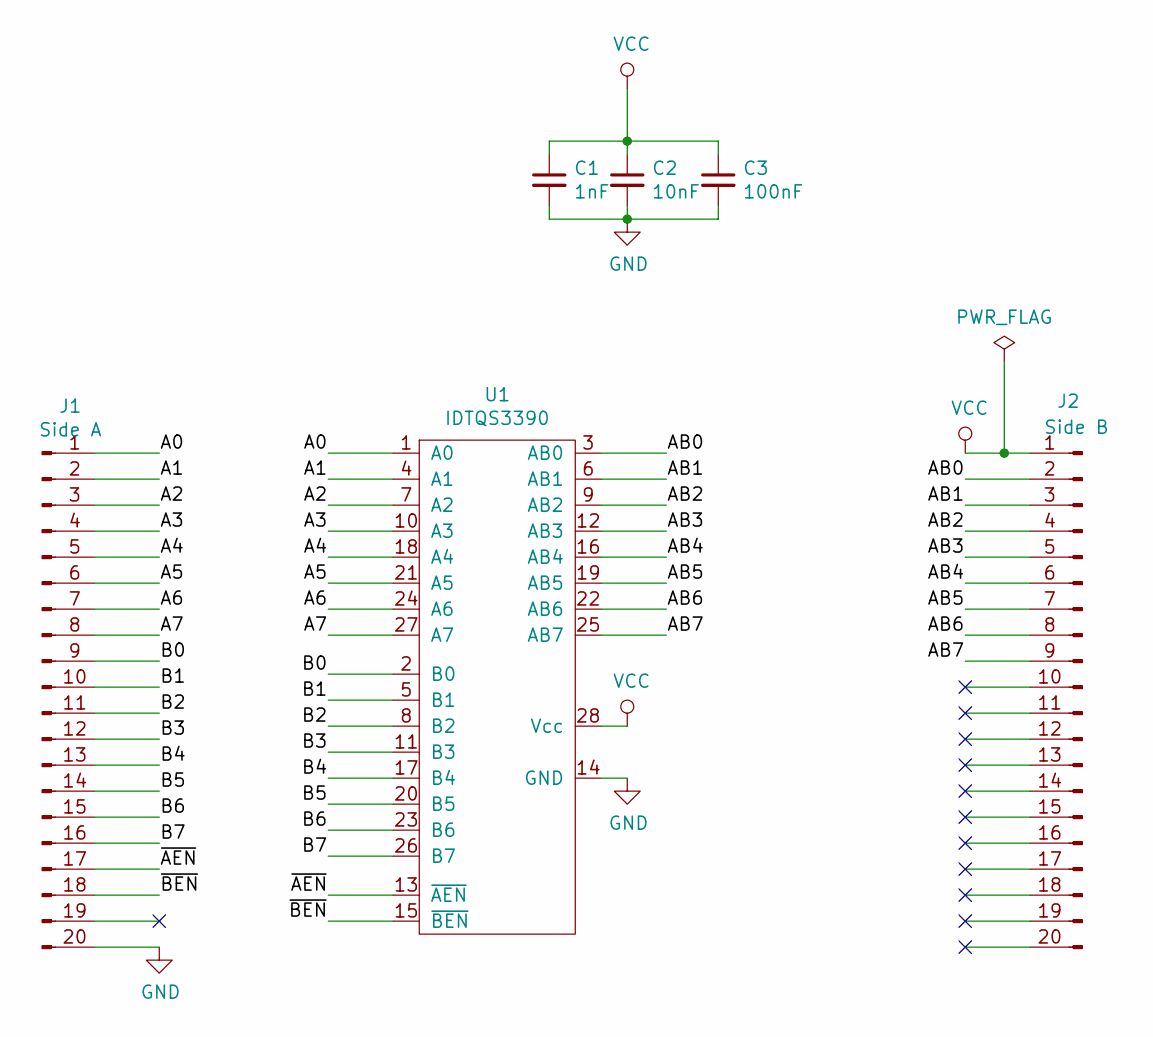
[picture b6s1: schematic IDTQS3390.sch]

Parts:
C1: 1nF; C_0805_2012Metric_Pad1.15x1.40mm_HandSolder
C2: 10nF; C_0805_2012Metric_Pad1.15x1.40mm_HandSolder
C3: 100nF; C_0805_2012Metric_Pad1.15x1.40mm_HandSolder
J1: Side A; PinHeader_1x20_P2.54mm_Vertical
J2: Side B; PinHeader_1x20_P2.54mm_Vertical
U1: IDTQS3390; SSOP-28_3.9x9.9mm_P0.635mm

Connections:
/A0: J1.1, U1.1 (A0)
/A1: J1.2, U1.4 (A1)
/A2: J1.3, U1.7 (A2)
/A3: J1.4, U1.10 (A3)
/A4: J1.5, U1.18 (A4)
/A5: J1.6, U1.21 (A5)
/A6: J1.7, U1.24 (A6)
/A7: J1.8, U1.27 (A7)
/AB0: J2.2, U1.3 (AB0)
/AB1: J2.3, U1.6 (AB1)
/AB2: J2.4, U1.9 (AB2)
/AB3: J2.5, U1.12 (AB3)
/AB4: J2.6, U1.16 (AB4)
/AB5: J2.7, U1.19 (AB5)
/AB6: J2.8, U1.22 (AB6)
/AB7: J2.9, U1.25 (AB7)
/B0: J1.9, U1.2 (B0)
/B1: J1.10, U1.5 (B1)
/B2: J1.11, U1.8 (B2)
/B3: J1.12, U1.11 (B3)
/B4: J1.13, U1.17 (B4)
/B5: J1.14, U1.20 (B5)
/B6: J1.15, U1.23 (B6)
/B7: J1.16, U1.26 (B7)
/~AEN: J1.17, U1.13 (~AEN)
/~BEN: J1.18, U1.15 (~BEN)
GND: C1.2, C2.2, C3.2, J1.20, U1.14 (GND)
VCC: C1.1, C2.1, C3.1, J2.1, U1.28 (Vcc)

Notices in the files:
parts and their libraries:
Copyright 2016 Accelerated Designs. All rights reserved.
